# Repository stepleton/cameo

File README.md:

# Cameo

is a peripheral [cape](https://beagleboard.org/capes) circuit board that allows
the [PocketBeagle](http://beagleboard.org/pocket) single-board computer (which
uses 3.3V digital signals) to interface with 5V digital logic. It is built
around two Texas Instruments [TXS0108EPWR]( http://www.ti.com/product/TXS0108E)
or [TXB0108PWR]( http://www.ti.com/product/TXB0108) 8-bit bidirectional voltage
level translator ICs. Sixteen digital I/O signal lines are available.

Cameo is optimised for applications that take advantage of the two [PRU-ICSS](
https://beagleboard.org/pru) real-time coprocessors built into the chip-like
hybrid circuit that powers the PocketBeagle (a [TI AM3358](
http://www.ti.com/product/AM3358) SoC/[Octavo OSD3358](
https://octavosystems.com/octavo_products/osd335x/) SiP). The digital I/O lines
that pass through Cameo include all fourteen logic lines the PRUs can access
directly in either the input or output direction. The two remaining lines are
one that PRU 0 can use for output only and one it can use for input only, the
latter of which also happens to be the CLOCKIN line for the PRU's "parallel
capture" input mode. Alternatively, all lines may be used bidirectionally via
the AM3358's GPIO modules.

Cameo is "plugboard programmable": a pattern of jumper pads on the cape allow
each signal line to be individually tied/pulled to GND or +5V, or to be
[terminated](https://www.youtube.com/watch?v=rN9zjVK3Nrk) in a variety of ways,
all through installation of appropriate 0603 surface-mount components (or, in a
pinch, solder bridges or small fragments of wire). See the [plugboard pad map](
#plugboard-pad-map) for a diagram showing all of the "plugboard" pads.

## Fair warning

Cameo and associated hardware designs, software materials, and other resources
distributed alongside it are all made available for free with NO WARRANTY OF
ANY KIND. Any system that interfaces with Cameo could suffer malfunction, data
loss, physical damage, or other harms. Some of these effects could be permanent
and/or unrepairable. If you're not prepared to risk these consequences, don't
use Cameo.

## Example applications

* [ Aphid](aphid/),
  a hardware emulator for Apple parallel port hard drives.

## Assembly and installation

Cameo is designed to mount underneath the PocketBeagle, preserving easy access
to the PocketBeagle's soft power button. The pin header for 5V digital I/O is
mounted on the underside of Cameo. With a short ribbon cable like the one in
the photo, the entire lightweight "stack" can dangle from a computer peripheral
port, as long as clearances and the security/fastness of the connector allow.

### Costs

To build a ready-to-use "stack" of your own from parts, you will need (prices
for informational purposes only; many are likely out-of-date):

* A PocketBeagle compact single-board computer ($25)
* A Cameo printed circuit board ($10 per board, **but sold only in packs of 3**
  from [OSH Park](https://www.oshpark.com/shared_projects/51GWu9Kw); shop around
  for deals by uploading the Gerber or KiCad project files in the
  [hardware directory](hardware) to online PCB manufacturers)
* Two TXS0108EPWR bidirectional level translator ICs ([e.g.](
  https://www.digikey.com/short/jr94zw); $1.66 each)
* Four 0.1μF MLCC 0603 surface mount capacitors ([e.g.](
  https://www.digikey.com/short/jr9znz); $0.10 each)
* One 240kΩ 0603 surface mount resistor ([e.g.](
  https://www.digikey.com/short/jrvd8z); $0.10 for just one)
* One 2x13 0.1" pitch pin header ([e.g.](https://www.digikey.com/short/jr9439);
  plastic shroud at your discretion; $0.30)
* Two 2x18 0.1" pitch pin headers ([e.g.](https://www.digikey.com/short/jr94b9);
  $0.69 each)
* Two 2x18 0.1" pitch sockets ([e.g.](https://www.digikey.com/short/jr94rq);
  $2.06 each)
* microSD memory card, 4GB or more, class 10 or better ($7 or so)
* Jumper and termination 0603 surface-mount components for I/O pins as required
  by your application (assuming the [Aphid](aphid/) configuration with 3 0Ω
  jumpers ([e.g.](https://www.digikey.com/short/jr9m80)) and 13 100Ω inline
  terminating resistors ([e.g.](https://www.digikey.com/short/j1rr2w)), $0.53
  altogether; jumpers are free if you make your own from scrap wire)

costing $52.15 in total. If you are willing to bond the PocketBeagle and Cameo
together permanently, you can omit the 2x18 sockets and save a bit over $4.

Some applications may benefit from adapting the 26-pin header on the bottom of
Cameo to a 25-pin DB-25 plug connector. To make this adaptor, you can use:

* 2x13 0.1" pitch socket with IDC crimp termination ([e.g.](
  https://www.digikey.com/short/jrbw3d), $0.58)
* DB-25 plug connector with IDC crimp termination ([e.g.](
  https://www.digikey.com/short/jrb2dj), $2.33)
* A short length (around 5cm) of 26-pin ribbon cable. ([e.g.](
  https://www.digikey.com/short/jrb2rr); $1.28 for a foot, ideally scrounged
  from a junk drawer for free)

adding to an additional $4.19.

### Assembly

Cameo is not an ideal starter project for hobbyists new to soldering
surface-mounted components; on the other hand, it doesn't have too many of
them, and they're not very tightly packed. The following diagram shows the
locations of essential SMD components on Cameo:

More SMD components will be required to set up the "plugboard" that connects
PocketBeagle signal lines to pins on the 5V I/O header. The specific nature and
configuration of these components are application-specific. See the
[introduction](#cameo) and the [plugboard pad map](#plugboard-pad-map) for more
details of the plugboard.

When assembling the Cameo board, it may be advisable to place the two voltage
translator ICs first, followed by the discrete SMD components and then by the
through-hole headers/connectors. **Remember, Cameo expects to be slung
underneath the PocketBeagle, so the 5V I/O header (centre) should emerge from
the bottom of the board, while the headers (or sockets) for connecting to the
PocketBeagle should emerge from the top.**

To connect to Cameo, the PocketBeagle will need sockets (or headers) emerging
from the **bottom** of its PCB. When mating Cameo to the PocketBeagle, be
certain of the correct orientation: if Cameo is orientated as shown above, the
USB connector on the PocketBeagle should be visible and pointing leftward.

Refer to online tutorials for making ribbon cable assemblies with IDC
connectors ([e.g.](https://startingelectronics.org/articles/IDC-ribbon-cable/))
to build an adaptor for the 5V I/O header. In general, it's best for the cable
between the two connectors to be as short as possible.

## Header pinout

The following pinout diagram represents Cameo's 26-pin 5V I/O header as viewed
from the underside of the Cameo PCB, with the PocketBeagle's USB connector
pointing upward.

| GPIO | PRU | PB pin | |   Name | I/O pin | I/O pin | Name   | | PB pin | PRU | GPIO |
|-----:|----:|-------:|-|-------:|:-------:|:-------:|:-------|-|:-------|:----|:-----|
|      |     |        | | _n/c_  |  **1**  |  **2**  |  PEX3  | | P1.35  | 1 ⇆ | 2.24 |
| 1.10 | ⇆ 1 |  P1.32 | |  PEX1  |  **3**  |  **4**  | \PSTRB | | P2.9   | 0 ← | 0.15 |
| 1.11 | ⇆ 1 |  P1.30 | | PR/\W  |  **5**  |  **6**  | \PBSY  | | P2.35  | 1 ⇆ | 2.22 |
| 2.25 | ⇆ 1 |   P1.4 | |  PEX2  |  **7**  |  **8**  | \PCMD  | | P1.2   | 1 ⇆ | 2.23 |
| 3.14 | ⇆ 0 |  P1.36 | |   PD0  |  **9**  | **10**  |\PPARITY| | P2.24  | 0 → | 1.12 |
| 3.15 | ⇆ 0 |  P1.33 | |   PD1  |  **11** | **12**  |   ⏚    | |        |     |      |
|      |     |        | |  _n/c_ |  **13** | **14**  |   ⏚    | |        |     |      |
| 3.16 | ⇆ 0 |  P2.32 | |   PD2  |  **15** | **16**  | _n/c_  | |        |     |      |
|      |     |        | |    ⏚   |  **17** | **18**  |  PD3   | | P2.30  | 0 ⇆ | 3.17 |
|      |     |        | |    ⏚   |  **19** | **20**  |  PD4   | | P1.31  | 0 ⇆ | 3.18 |
| 3.19 | ⇆ 0 |  P2.34 | |   PD5  |  **21** | **22**  |   ⏚    | |        |     |      |
| 3.20 | ⇆ 0 |  P2.28 | |   PD6  |  **23** | **24**  |   ⏚    | |        |     |      |
| 3.21 | ⇆ 0 |  P1.29 | |   PD7  |  **25** | **26**  |   ⏚    | |        |     |      |

The names of the 5V I/O pins reflect one of the example applications and should
be considered arbitrary. Pins marked _n/c_ connect to nothing; pins marked ⏚
are tied to ground.

The "PB pin" column shows which PocketBeagle header pin connects to Cameo's 5V
I/O header (through the 3.3V ⇆ 5V bidirectional voltage level translator ICs).

The "PRU" columns show which of the two PRU-ICSS real-time coprocessors in the
AM3358 are connected to each pin. A ⇆ symbol means that the corresponding
PocketBeagle pin can be configured either as an input to or an output of the
PRU; the ← and → symbols mean that the pin can only be a PRU input or output
respectively. Pins PD0-PD7 in particular map to PRU 0 GPIO bits 0-7.

The "GPIO" columns show how the pins correspond to I/O bits in the AM3358's
GPIO modules ("3.21" means module 3, bit 21). All pins may be accessed in any
direction through the GPIO subsystem.

For more detailed connectivity information, refer to the expansion header
tables in the [PocketBeagle reference manual](
https://github.com/beagleboard/pocketbeagle/wiki/System-Reference-Manual#71_Expansion_Header_Connectors).

Note finally that if an ordinary ribbon cable is used in an adaptor that
connects the 5V I/O header to a DB-25 plug connector, the pin numbering
patterns for both are different:

| DB-25 pin  | 1 | 2 | 3 | 4 | 5 |  6 |  7 |  8 |  9 | 10 | 11 | 12 | 13 |
|------------|---|---|---|---|---|----|----|----|----|----|----|----|----|
| Header pin | 1 | 3 | 5 | 7 | 9 | 11 | 13 | 15 | 17 | 19 | 21 | 23 | 25 |

| DB-25 pin  | 14 | 15 | 16 | 17 | 18 | 19 | 20 | 21 | 22 | 23 | 24 | 25 |
|------------|----|----|----|----|----|----|----|----|----|----|----|----|
| Header pin |  2 |  4 |  6 |  8 | 10 | 12 | 14 | 16 | 18 | 20 | 22 | 24 |

## Plugboard pad map

This diagram shows a top-side view of Cameo. (In this view, the through-holes
for the 26-pin 5V I/O header (centre) are "flipped" about the header's long
(horizontal) axis, since the pins emerge from the underside of the board.)

The installation of jumpers, resistors, or other 0603 surface mount components
on each set of five pads shaped like ⠾, ⠻, or ⠷ determines whether and how the
labelled pin connects (through the voltage translator ICs) to the PocketBeagle.

## Development

Cameo was designed with [KiCad](http://kicad-pcb.org/) 4.  Project files and
derived products (Gerber files, etc.) are kept in the [hardware](hardware/)
subdirectory.

## Other notes

To the fullest extent possible, Cameo is released into the public domain.
Nobody owns Cameo.

## Acknowledgements

It would not have been possible for me to design Cameo without the help of the
following people and resources:

* Michael Welling's [pocketbeagle-cape-template](
  https://github.com/mwelling/pocketbeagle-cape-template).
* The [Sitara Processors Forum](https://e2e.ti.com/support/arm/sitara_arm) on
  the [TI E2E Community](https://e2e.ti.com/).
* Anonymous friends.

-- [_Tom Stepleton_](mailto:stepleton@gmail.com), 11 August 2018, London

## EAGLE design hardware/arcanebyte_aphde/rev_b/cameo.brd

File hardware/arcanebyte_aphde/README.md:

# Apple Parallel Hard Drive Emulator

The Apple Parallel Hard Drive Emulator is derived from the Cameo/Aphid cape
for the [PocketBeagle](http://beagleboard.org/pocket) single-board computer.
It is intended as a modified form-factor with some enhancements over the
cape design.

## Rev A

The Rev A design uses the same components as the cape, including two Texas
Instruments [TXS0108EPWR]( http://www.ti.com/product/TXS0108E) 8-bit bidirectional voltage
level translator ICs. The 100ohm resistors are included for better
compatibility with the Lisa 2/10, but YMMV. The board is designed to plug
directly into the parallel port without a cable.

## Rev B

The Rev B design forgoes the TXS0108 chips for BSS138 logic level converters.
This design has shown to be more compatible with the Apple Lisa 2/10 using the
internal widget cable. A small adapter can be used to convert from the 26-pin
IDC cable to the DB25 interface provided on the board.

## Other notes

In the spirit of Cameo, this modified design is released into the public domain.
There is no warranty and any improvements are welcome.

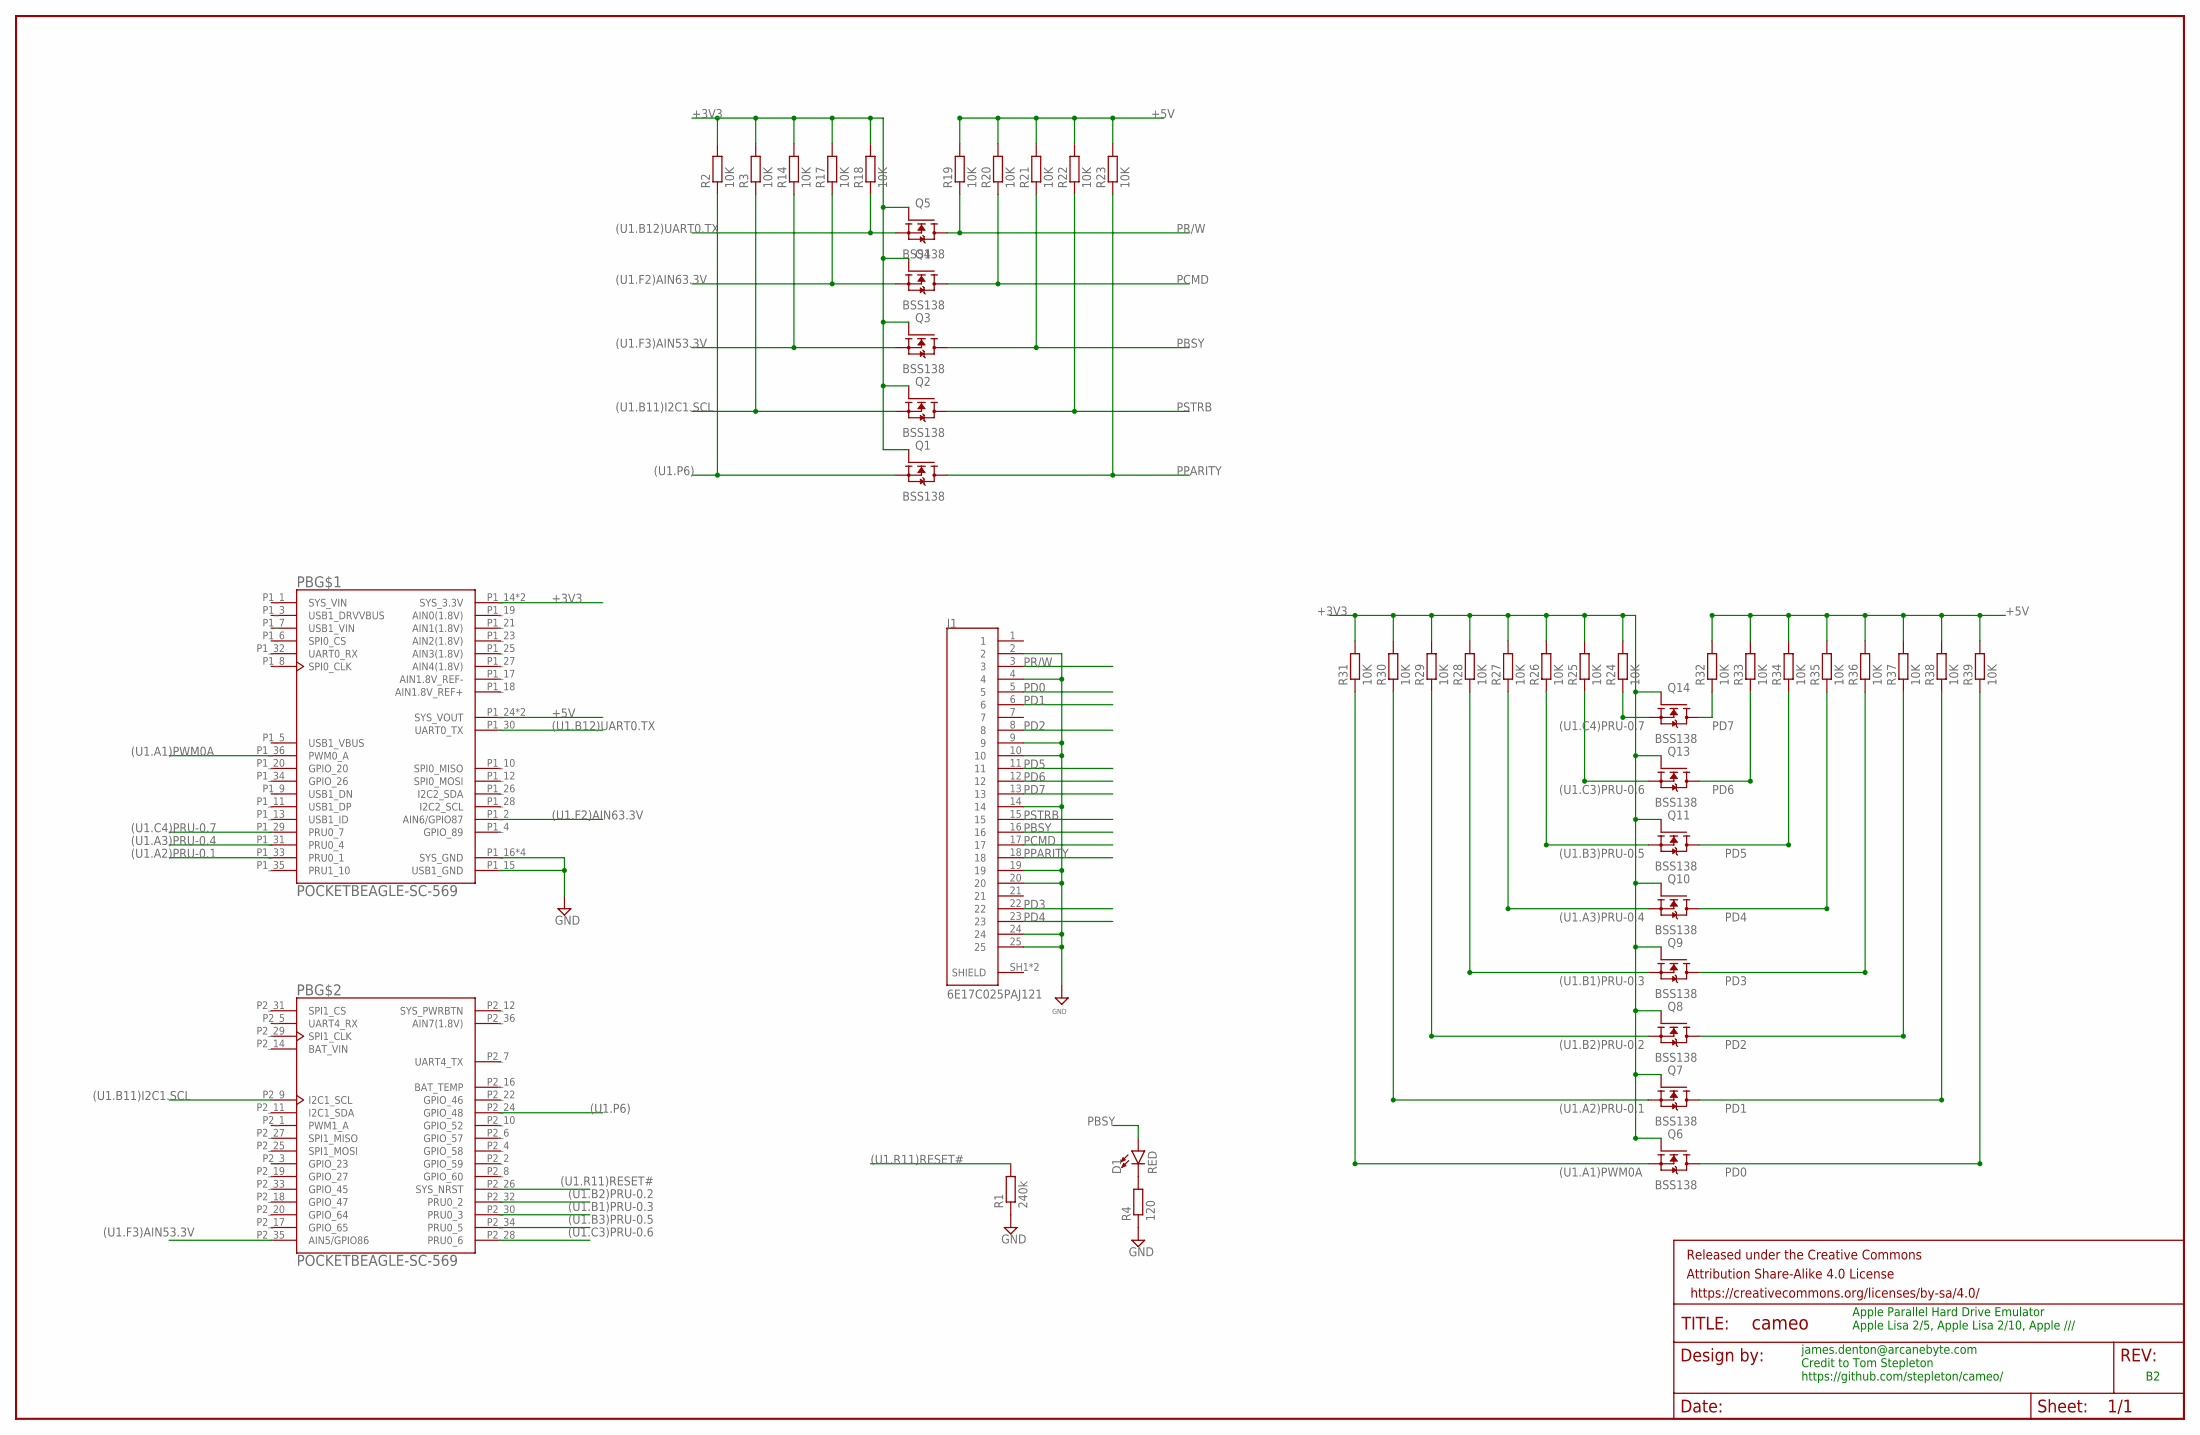
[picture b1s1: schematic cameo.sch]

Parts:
D1: RED; LED-0603
FRAME1: FRAME-LEDGER; CREATIVE_COMMONS
J1: 6E17C025PAJ121; CONN_6E17C025PAJ121
PB: POCKETBEAGLE-SC-569; BEAGLE_POCKETBEAGLE-SC-569
Q1, Q2, Q3, Q4, Q5, Q6, Q7, Q8, Q9, Q10, Q11, Q13, Q14: BSS138; SOT95P240X111-3N
R1: 240k; R0603
R2, R3, R14, R17, R18, R19, R20, R21, R22, R23, R24, R25, R26, R27, R28, R29, R30, R31, R32, R33, R34, R35, R36, R37, R38, R39: 10K; R0603
R4: 120; R0603

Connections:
(U1.A1)PWM0A: PB.P1_36 (PWM0_A), Q6.2 (S), R31.1
(U1.A2)PRU-0.1: PB.P1_33 (PRU0_1), Q7.2 (S), R30.1
(U1.A3)PRU-0.4: PB.P1_31 (PRU0_4), Q10.2 (S), R27.1
(U1.B1)PRU-0.3: PB.P2_30 (PRU0_3), Q9.2 (S), R28.1
(U1.B2)PRU-0.2: PB.P2_32 (PRU0_2), Q8.2 (S), R29.1
(U1.B3)PRU-0.5: PB.P2_34 (PRU0_5), Q11.2 (S), R26.1
(U1.B11)I2C1.SCL: PB.P2_9 (I2C1_SCL), Q2.2 (S), R3.1
(U1.B12)UART0.TX: PB.P1_30 (UART0_TX), Q5.2 (S), R18.1
(U1.C3)PRU-0.6: PB.P2_28 (PRU0_6), Q13.2 (S), R25.1
(U1.C4)PRU-0.7: PB.P1_29 (PRU0_7), Q14.2 (S), R24.1
(U1.F2)AIN63.3V: PB.P1_2 (AIN6/GPIO87), Q4.2 (S), R17.1
(U1.F3)AIN53.3V: PB.P2_35 (AIN5/GPIO86), Q3.2 (S), R14.1
(U1.P6): PB.P2_24 (GPIO_48), Q1.2 (S), R2.1
(U1.R11)RESET#: PB.P2_26 (SYS_NRST), R1.2
+3V3: PB.P1_14 (SYS_3.3V), PB.P2_23 (SYS_3.3V), Q1.1 (G), Q2.1 (G), Q3.1 (G), Q4.1 (G), Q5.1 (G), Q6.1 (G), Q7.1 (G), Q8.1 (G), Q9.1 (G), Q10.1 (G), Q11.1 (G), Q13.1 (G), Q14.1 (G), R2.2, R3.2, R14.2, R17.2, R18.2, R24.2, R25.2, R26.2, R27.2, R28.2, R29.2, R30.2, R31.2
+5V: PB.P1_24 (SYS_VOUT), PB.P2_13 (SYS_VOUT), R19.2, R20.2, R21.2, R22.2, R23.2, R32.2, R33.2, R34.2, R35.2, R36.2, R37.2, R38.2, R39.2
AIN0(1.8V): PB.P1_19 (AIN0(1.8V))
AIN1(1.8V): PB.P1_21 (AIN1(1.8V))
AIN1.8V_REF+: PB.P1_18 (AIN1.8V_REF+)
AIN1.8V_REF-: PB.P1_17 (AIN1.8V_REF-)
AIN2(1.8V): PB.P1_23 (AIN2(1.8V))
AIN3(1.8V): PB.P1_25 (AIN3(1.8V))
AIN4(1.8V): PB.P1_27 (AIN4(1.8V))
AIN7(1.8V): PB.P2_36 (AIN7(1.8V))
GND: J1.2, J1.4, J1.9, J1.10, J1.14, J1.19, J1.20, J1.24, J1.25, PB.P1_15 (USB1_GND), PB.P1_16 (SYS_GND), PB.P1_22 (SYS_GND), PB.P2_15 (SYS_GND), PB.P2_21 (SYS_GND), R1.1, R4.1
unnamed: D1.C, R4.2
PBSY: D1.A, J1.16, Q3.3 (D), R21.1
PCMD: J1.17, Q4.3 (D), R20.1
PD0: J1.5, Q6.3 (D), R39.1
PD1: J1.6, Q7.3 (D), R38.1
PD2: J1.8, Q8.3 (D), R37.1
PD3: J1.22, Q9.3 (D), R36.1
PD4: J1.23, Q10.3 (D), R35.1
PD5: J1.11, Q11.3 (D), R34.1
PD6: J1.12, Q13.3 (D), R33.1
PD7: J1.13, Q14.3 (D), R32.1
PPARITY: J1.18, Q1.3 (D), R23.1
PR/W: J1.3, Q5.3 (D), R19.1
PSTRB: J1.15, Q2.3 (D), R22.1
SYS_PWRBTN: PB.P2_12 (SYS_PWRBTN)

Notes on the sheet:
james.denton@arcanebyte.com Credit to Tom Stepleton https://github.com/stepleton/cameo/
Apple Parallel Hard Drive Emulator Apple Lisa 2/5, Apple Lisa 2/10, Apple ///

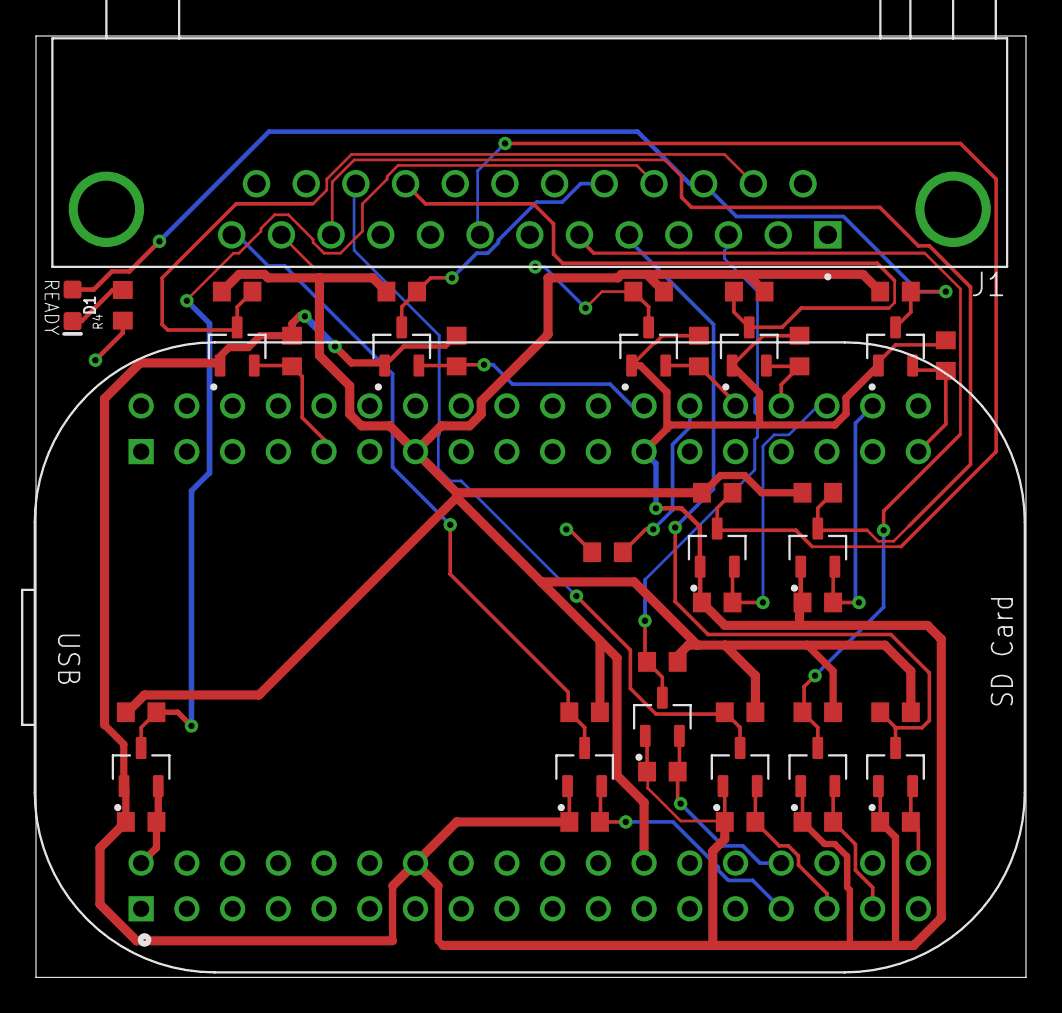
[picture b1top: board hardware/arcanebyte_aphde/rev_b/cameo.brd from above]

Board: 2 copper layers, 55.0 x 52.3 mm, 45 parts (0 on the bottom side), 31 nets.

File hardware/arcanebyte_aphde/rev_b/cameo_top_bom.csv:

Comment,Designator,Footprint,LCSC Part #
10K,R2 R3 R14 R17 R18 R19 R20 R21 R22 R23 R24 R25 R26 R27 R28 R29 R30 R31 R32 R33 R34 R35 R36 R37 R38 R39,R0603,
120,R4,R0603,
240k,R1,R0603,
BSS138,Q1 Q2 Q3 Q4 Q5 Q6 Q7 Q8 Q9 Q10 Q11 Q13 Q14,SOT95P240X111-3N,
RED,D1,LED-0603,C72044

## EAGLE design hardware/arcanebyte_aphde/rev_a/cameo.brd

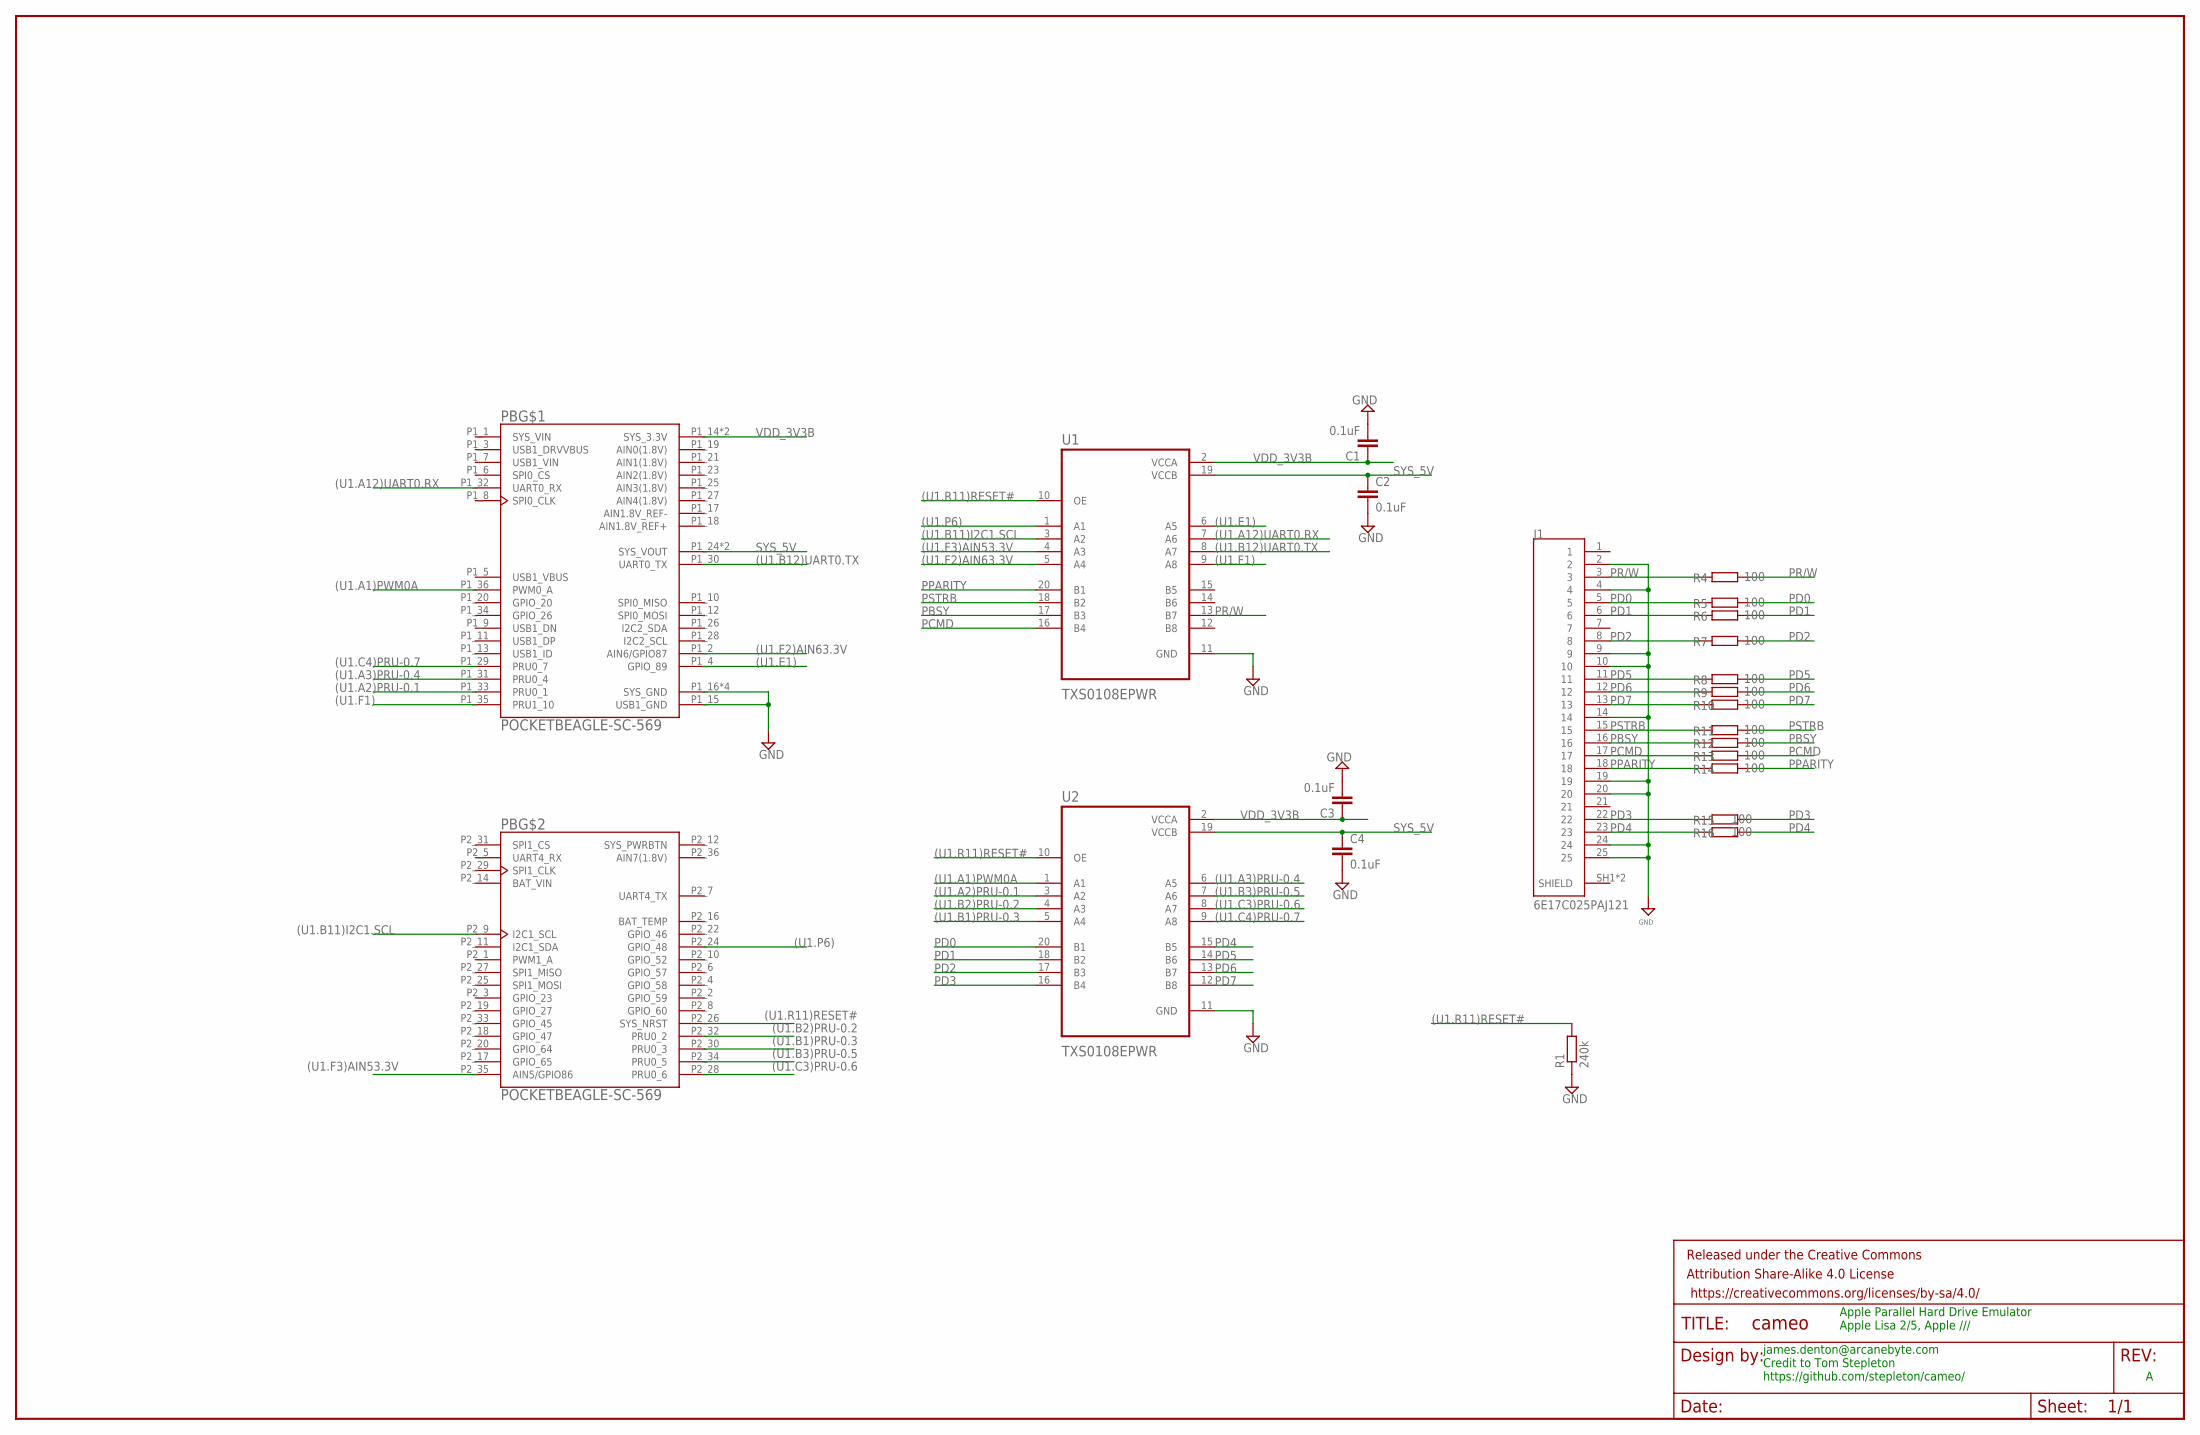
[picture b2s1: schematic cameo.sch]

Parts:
C1, C2, C3, C4: 0.1uF; C0603
FRAME1: FRAME-LEDGER; CREATIVE_COMMONS
J1: 6E17C025PAJ121; CONN_6E17C025PAJ121
PB: POCKETBEAGLE-SC-569; BEAGLE_POCKETBEAGLE-SC-569
R1: 240k; R0603
R4, R5, R6, R7, R8, R9, R10, R11, R12, R13, R14, R15, R16: 100; R0603
U1, U2: TXS0108EPWR; SOP65P640X120-20N

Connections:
(U1.A1)PWM0A: PB.P1_36 (PWM0_A), U2.1 (A1)
(U1.A2)PRU-0.1: PB.P1_33 (PRU0_1), U2.3 (A2)
(U1.A3)PRU-0.4: PB.P1_31 (PRU0_4), U2.6 (A5)
(U1.A12)UART0.RX: PB.P1_32 (UART0_RX), U1.7 (A6)
(U1.B1)PRU-0.3: PB.P2_30 (PRU0_3), U2.5 (A4)
(U1.B2)PRU-0.2: PB.P2_32 (PRU0_2), U2.4 (A3)
(U1.B3)PRU-0.5: PB.P2_34 (PRU0_5), U2.7 (A6)
(U1.B11)I2C1.SCL: PB.P2_9 (I2C1_SCL), U1.3 (A2)
(U1.B12)UART0.TX: PB.P1_30 (UART0_TX), U1.8 (A7)
(U1.C3)PRU-0.6: PB.P2_28 (PRU0_6), U2.8 (A7)
(U1.C4)PRU-0.7: PB.P1_29 (PRU0_7), U2.9 (A8)
(U1.E1): PB.P1_4 (GPIO_89), U1.6 (A5)
(U1.F1): PB.P1_35 (PRU1_10), U1.9 (A8)
(U1.F2)AIN63.3V: PB.P1_2 (AIN6/GPIO87), U1.5 (A4)
(U1.F3)AIN53.3V: PB.P2_35 (AIN5/GPIO86), U1.4 (A3)
(U1.P6): PB.P2_24 (GPIO_48), U1.1 (A1)
(U1.R11)RESET#: PB.P2_26 (SYS_NRST), R1.2, U1.10 (OE), U2.10 (OE)
AIN0(1.8V): PB.P1_19 (AIN0(1.8V))
AIN1(1.8V): PB.P1_21 (AIN1(1.8V))
AIN1.8V_REF+: PB.P1_18 (AIN1.8V_REF+)
AIN1.8V_REF-: PB.P1_17 (AIN1.8V_REF-)
AIN2(1.8V): PB.P1_23 (AIN2(1.8V))
AIN3(1.8V): PB.P1_25 (AIN3(1.8V))
AIN4(1.8V): PB.P1_27 (AIN4(1.8V))
AIN7(1.8V): PB.P2_36 (AIN7(1.8V))
GND: C1.2, C2.2, C3.2, C4.2, J1.2, J1.4, J1.9, J1.10, J1.14, J1.19, J1.20, J1.24, J1.25, PB.P1_15 (USB1_GND), PB.P1_16 (SYS_GND), PB.P1_22 (SYS_GND), PB.P2_15 (SYS_GND), PB.P2_21 (SYS_GND), R1.1, U1.11 (GND), U2.11 (GND)
PBSY: J1.16, R12.1, R12.2, U1.17 (B3)
PCMD: J1.17, R13.1, R13.2, U1.16 (B4)
PD0: J1.5, R5.1, R5.2, U2.20 (B1)
PD1: J1.6, R6.1, R6.2, U2.18 (B2)
PD2: J1.8, R7.1, R7.2, U2.17 (B3)
PD3: J1.22, R15.1, R15.2, U2.16 (B4)
PD4: J1.23, R16.1, R16.2, U2.15 (B5)
PD5: J1.11, R8.1, R8.2, U2.14 (B6)
PD6: J1.12, R9.1, R9.2, U2.13 (B7)
PD7: J1.13, R10.1, R10.2, U2.12 (B8)
PPARITY: J1.18, R14.1, R14.2, U1.20 (B1)
PR/W: J1.3, R4.1, R4.2, U1.13 (B7)
PSTRB: J1.15, R11.1, R11.2, U1.18 (B2)
SYS_5V: C2.1, C4.1, PB.P1_24 (SYS_VOUT), PB.P2_13 (SYS_VOUT), U1.19 (VCCB), U2.19 (VCCB)
SYS_PWRBTN: PB.P2_12 (SYS_PWRBTN)
VDD_3V3B: C1.1, C3.1, PB.P1_14 (SYS_3.3V), PB.P2_23 (SYS_3.3V), U1.2 (VCCA), U2.2 (VCCA)

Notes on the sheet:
james.denton@arcanebyte.com Credit to Tom Stepleton https://github.com/stepleton/cameo/
Apple Parallel Hard Drive Emulator Apple Lisa 2/5, Apple ///

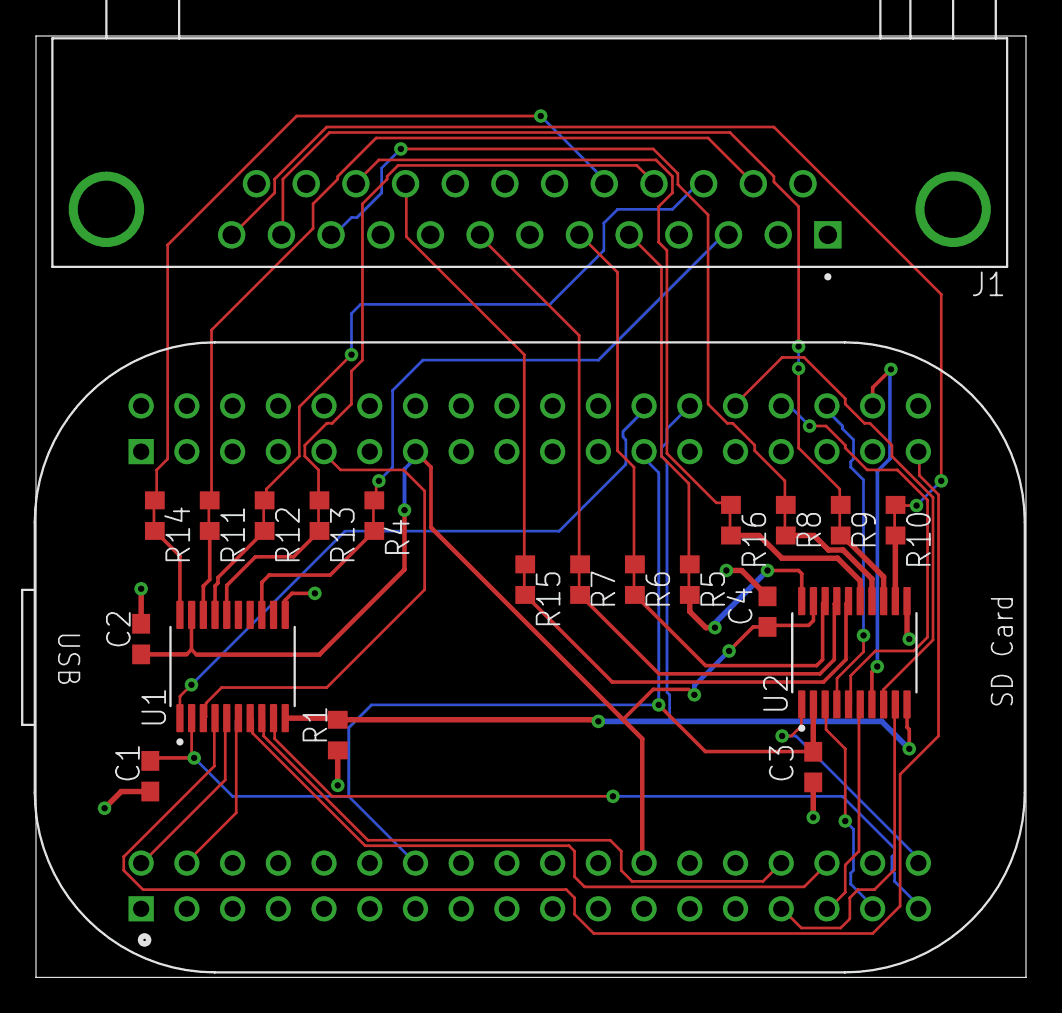
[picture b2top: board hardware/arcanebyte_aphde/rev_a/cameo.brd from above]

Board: 2 copper layers, 55.0 x 52.3 mm, 23 parts (0 on the bottom side), 33 nets.

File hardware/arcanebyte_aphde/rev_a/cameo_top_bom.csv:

Comment,Designator,Footprint,LCSC Part #
0.1uF,C1 C2 C3 C4,C0603,
100,R4 R5 R6 R7 R8 R9 R10 R11 R12 R13 R14 R15 R16,R0603,
240k,R1,R0603,
TXS0108EPWR,U1 U2,SOP65P640X120-20N,C17206

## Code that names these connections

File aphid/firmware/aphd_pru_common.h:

/* Apple parallel port storage emulator for Cameo
 *
 * Forfeited into the public domain with NO WARRANTY. Read LICENSE for details.
 *
 * This file: constants and other shared information for both PRU programs.
 *
 * Comments may refer to various manuals by abbreviations:
 *    TRM: AM335x Technical Reference Manual
 *    PRG: AM335x PRU Reference Guide
 */

#ifndef APHD_PRU_COMMON_H_
#define APHD_PRU_COMMON_H_


/* //////////////////////
//// I/O PIN ALIASES ////
////////////////////// */

/* Control lines are unidirectional, so we can refer to them via constants
 * whether we are retrieving or sending data. */

#define pBSY      r30.t8
#define psBSY     "r30.t8"
#define ppBSY     8

#define pCMD      r31.t9
#define psCMD     "r31.t9"
#define ppCMD     9

#define pPARITY   r30.t14
#define psPARITY  "r30.t14"
#define ppPARITY  14

#define pRW       r31.t15    /* NOTE: This signal is PEX2 on the schematic, */
#define psRW      "r31.t15"  /* not PR/\W. */
#define ppRW      15

#define pSTRB     r31.t16
#define psSTRB    "r31.t16"
#define ppSTRB    16


/* /////////////////////////
//// INTERRUPT HANDLING ////
///////////////////////// */

#define ePRU0to1 16U  /* System event for interrupts from PRU0 to PRU1 */
#define ePRU1to0 17U  /* System event for interrupts from PRU1 to PRU0 */
#define ePRU1toARM 18U  /* System event for interrupts from PRU1 to ARM */
#define eARMtoPRU1 19U  /* System event for interrputs from ARM to PRU1 */
/* Note: The Linux kernel device tree for the Beagles specify system events
 * 16 and 17 for RPMsg kicks between PRU0 and the ARM, and system events
 * 18 and 19 for RPMsg kicks between PRU1 and the ARM. Events 16 and 18 go
 * to the ARM; events 17 and 19 go to the PRU. */

#define sPRU0to1 16U + ePRU0to1  /* For raising a PRU0 to PRU1 system event */
#define sPRU1to0 16U + ePRU1to0  /* For raising a PRU1 to PRU0 system event */
#define sARMtoPRU1 16U + eARMtoPRU1  /* For raising an ARM to PRU1 sysevent */

#define iAnyToPRU1 31U  /* R31 bit indicating any interrupt to PRU1 */
#define iPRU1to0 30U    /* R31 bit indicating an interrupt from PRU1 to PRU0 */
/* Note: The resource table must ultimately map:
 *   system event ePRU0to1 to host interrupt (iAnyToPRU1 - 30),
 *   system event ePRU1to0 to host interrupt (iPRU1to0 - 30), and
 *   system event eARMtoPRU1 to host interrupt (iAnyToPRU1 - 30)
 * for these definitions to be correct. */


/* ////////////////////
//// CONST ALIASES ////
//////////////////// */

/* Aliases for various const registers (PRG 5.2.1). */

#define cINTC    c0   /* Pointer to PRU INTC */
#define cCONFIG  c4   /* Pointer to PRU_SYSCFG */
#define cSHARED  c28  /* Pointer to shared PRU RAM */

/* Aliases for offsets from various const registers. */

#define oINTC_SICR 0x24  /* cINTC offset to SICR register */


/* /////////////////////////
//// DATA PUMP COMMANDS ////
///////////////////////// */

#define dREAD    0x00  /* Read a block of data from the data lines */
#define dWRITE   0x01  /* Write a block of data to the data lines */
#define dINVALID 0x80  /* An intentional nonsense command, used for resets */


#endif  /* APHD_PRU_COMMON_H_ */

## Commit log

2018-07-25 Delay message in README.md
2018-08-12 Cameo and Aphid full initial commit
2018-08-12 Correct resistor value in SMD component layout images.
2018-08-13 Correct the year in the main README.
2018-08-13 Correct the year in the Aphid README.
2018-10-04 Cameo/Aphid September 2018 update
2018-10-20 Update for the 2018-10-07 BeagleBoard.org image
    Plus a small progress report on signal termination for longer cables.
2018-12-07 Add 100Ω inline terminating resistors to most Aphid signal lines.
2019-11-06 Debian 9.9 disk image
2020-01-12 profile.py => python3; "conclusion" mechanism for restarting emulator from the Apple.
2021-01-17 Cameo/Aphid drive image selector: initial release
2021-01-17 Cosmetic Selector manual fixes
2021-01-23 Cameo/Aphid: Fix overly picky PRU1 state machine timing
    Waiting for a particular coincidence of \PCMD high and PR/\W low could lock up PRU0 for
    nearly 11 seconds if non-handshake activity on the control lines wiggled \PCMD and PR/\W
    together in a confusing way (specifically, in a way that left PR/\W high or had PR/\W go
    from low to high very quickly). The initialisation routine for the parallel interface
    card was prone to generating these toxic wiggles, but owing to vagaries of signal
    propagation and other electrical mysteries, a Cameo/Aphid device would only be affected
2021-01-23 Cameo/Aphid selector: HelloBootDrive interprets $00 drive IDs correctly on Lisa 2/10s
    012345678 012345678 012345678 012345678 012345678 012345678 012345678 012345678
    HelloBootDrive now converts device ID $00 to $02 on Lisa 2/10 systems, fixing a
    bug where the Selector would not believe on startup that the built-in parallel port
    (which it knows as $02) had a Cameo/Aphid attached.
2021-01-23 Cameo/Aphid selector: HelloBootDrive interprets $00 drive IDs as $02 on 2/10s
    HelloBootDrive now converts device ID $00 to $02 on Lisa 2/10 systems, fixing a
    bug where the Selector would not believe on startup that the built-in parallel
    port (which it knows as $02) had a Cameo/Aphid attached.
2021-01-24 Cameo/Aphid: New image, update docs, update installation scripts
2021-01-24 Cameo/Aphid Selector: 0.6, adds a S(elect command, docs updated
    Also renames the scripting command `Load` to `Read` to align with other
    nomenclature for usage of the key/value cache.
2021-01-30 Cameo/Aphid drive image selector: adds a screensaver, docs updated
2021-01-30 Cameo/Aphid drive image selector: add documentation screensaver image
2021-01-30 Cameo/Aphid drive image selector: update a screen depiction in manual
2021-01-30 Cameo/Aphid drive image selector: Final 0.7 manual corrections
2021-02-02 Cameo/Aphid: Device tree overlay + firmware autoload for fast boot
2021-02-06 Cameo/Aphid: support for ProFile-10 and nonstandard size drive images
2021-02-12 Cameo/Aphid: correct double-negative in firmware loading
2021-02-15 Cameo/Aphid: "No-timeout" PRU0 operation for better MacWorks compatibility
2021-02-16 Cameo/Aphid: Selector v0.8 and miscellaneous other convenience items
    Selector: Bounded status string printing to avoid screen mess if the Cameo/Aphid
    goes offline.
    Filesystem plugin: Addition of a 'mx' command for creating arbitrarily-sized
    drive images.
    Utility: addition of a diagnostic script for snooping on PRU1 by peeking into
    ARM/PRU shared memory space.
2021-02-24 Cameo/Aphid: Correct mis-assembly of the Selector
    The Selector floppy disk image should include the ProFile I/O library
    The Selector hard drive image should not
    It had been reversed, but it's corrected now
2021-02-27 Cameo/Aphid: Selector disk images now for both kinds of floppy
2021-02-27 Cameo/Aphid: Add a plugin that makes it easy to restore an overwritten Selector
2021-02-28 Cameo/Aphid Selector 0.9: image creation size option, and more
    Catalogue display shows the sizes of drive images
    Bugfix for text input setup when editing long strings
2021-02-28 Cameo/Aphid Selector 0.9: manual update
2021-02-28 Cameo/Aphid Selector 0.9: manual "picture" update
2021-02-28 Cameo/Aphid Selector 0.9: February is not a leap year
2021-03-28 Cameo/Aphid Selector 1.0: power button, floppy eject, autoboot password, bugfixes
2021-03-28 Cameo/Aphid Selector 1.0: fix missing documentation item
2021-06-19 Apple /// compatibility; Big Sur USB compatibility
2021-06-20 Correct credits in Aphid README
2021-09-08 added arcanebyte designs

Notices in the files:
parts and their libraries:
SparkFun-Aesthetics: Licensing: Creative Commons ShareAlike 4.0 International - https://creativecommons.org/licenses/by-sa/4.0
SparkFun-Aesthetics: Released under the Creative Commons Attribution Share-Alike 4.0 License
SparkFun-Aesthetics: https://creativecommons.org/licenses/by-sa/4.0
